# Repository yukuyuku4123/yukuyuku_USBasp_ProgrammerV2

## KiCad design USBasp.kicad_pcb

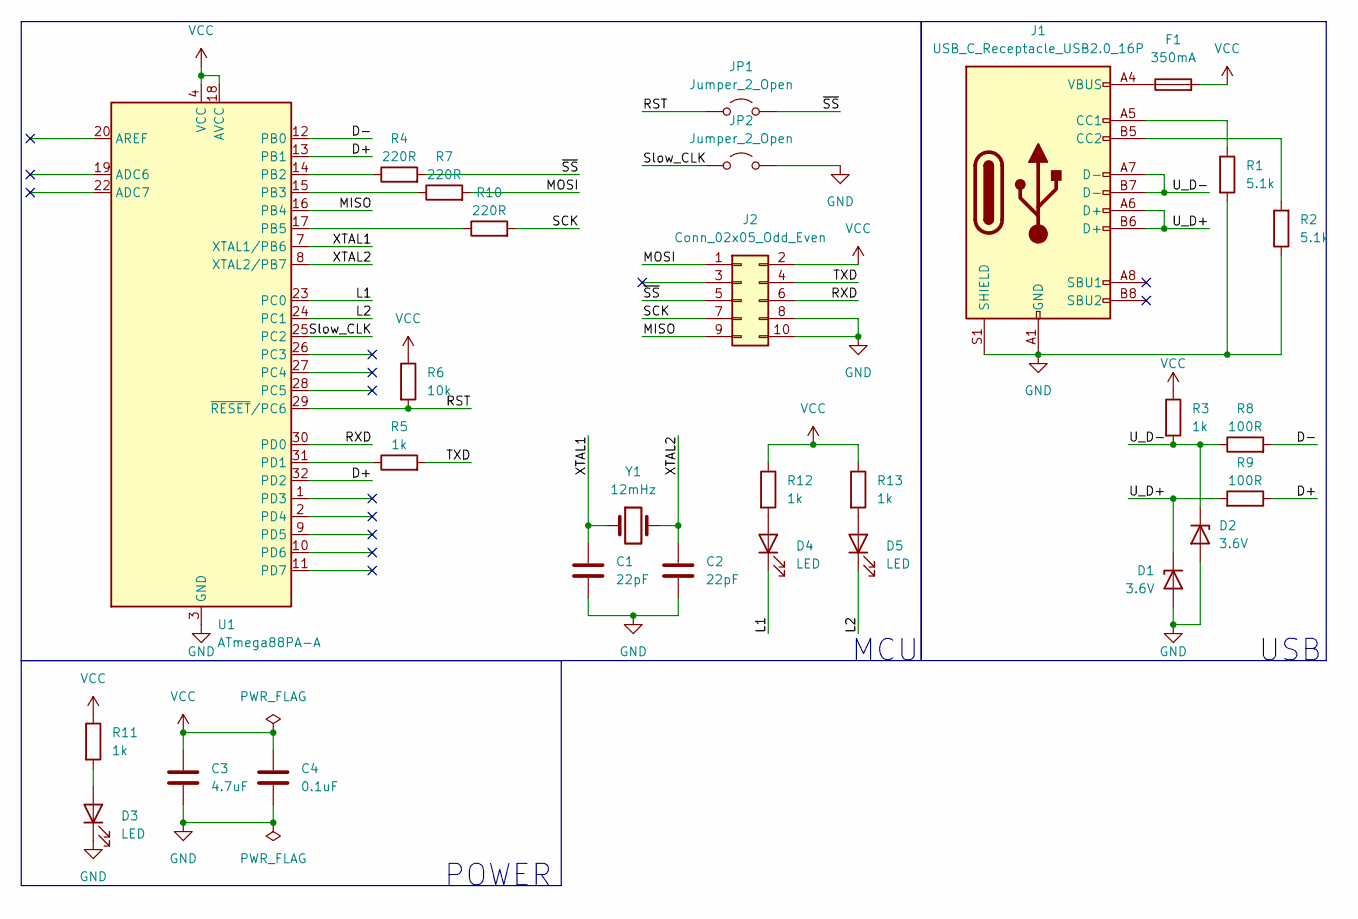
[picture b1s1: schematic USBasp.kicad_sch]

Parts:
C1, C2: 22pF; C_0402_1005Metric
C3: 4.7uF; C_0603_1608Metric
C4: 0.1uF; C_0402_1005Metric
D1, D2: 3.6V; D_SOD-323F
D3, D4, D5: LED; LED_0603_1608Metric
F1: 350mA; Fuse_0603_1608Metric
J1: USB_C_Receptacle_USB2.0_16P; USB_C_Receptacle_GCT_USB4105-xx-A_16P_TopMnt_Horizontal
J2: Conn_02x05_Odd_Even; PinHeader_2x05_P2.54mm_Vertical
JP1, JP2: Jumper_2_Open; PinHeader_1x02_P2.54mm_Vertical
R1, R2: 5.1k; R_0603_1608Metric
R3, R5, R11, R12, R13: 1k; R_0603_1608Metric
R4, R7, R10: 220R; R_0603_1608Metric
R6: 10k; R_0603_1608Metric
R8, R9: 100R; R_0603_1608Metric
U1: ATmega88PA-A; TQFP-32_7x7mm_P0.8mm
Y1: 12mHz; Crystal_HC49-4H_Vertical

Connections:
/D+: R9.1, U1.13 (PB1), U1.32 (PD2)
/D-: R8.2, U1.12 (PB0)
/L1: D4.1 (K), U1.23 (PC0)
/L2: D5.1 (K), U1.24 (PC1)
/MISO: J2.9, U1.16 (PB4)
/MOSI: J2.1, R7.2
/RST: JP1.1 (A), R6.2, U1.29 (~RESET/PC6)
/RXD: J2.6, U1.30 (PD0)
/SCK: J2.7, R10.2
/Slow_CLK: JP2.1 (A), U1.25 (PC2)
/TXD: J2.4, R5.2
/U_D+: D1.1 (K), J1.A6 (D+), J1.B6 (D+), R9.2
/U_D-: D2.1 (K), J1.A7 (D-), J1.B7 (D-), R3.2, R8.1
/XTAL1: C1.1, U1.7 (XTAL1/PB6), Y1.1
/XTAL2: C2.1, U1.8 (XTAL2/PB7), Y1.2
/~SS: J2.5, JP1.2 (B), R4.2
GND: C1.2, C2.2, C3.2, C4.2, D1.2 (A), D2.2 (A), D3.1 (K), J1.A1 (GND), J1.A12 (GND), J1.B1 (GND), J1.B12 (GND), J1.S1 (SHIELD), J2.8, J2.10, JP2.2 (B), R1.2, R2.1, U1.3 (GND), U1.5 (GND), U1.21 (GND)
unnamed: D3.2 (A), R11.2
unnamed: D4.2 (A), R12.2
unnamed: D5.2 (A), R13.2
unnamed: F1.1, J1.A4 (VBUS), J1.A9 (VBUS), J1.B4 (VBUS), J1.B9 (VBUS)
unnamed: J1.A5 (CC1), R1.1
unnamed: J1.B5 (CC2), R2.2
unnamed: R4.1, U1.14 (PB2)
unnamed: R7.1, U1.15 (PB3)
unnamed: R10.1, U1.17 (PB5)
unnamed: R5.1, U1.31 (PD1)
VCC: C3.1, C4.1, F1.2, J2.2, R3.1, R6.1, R11.1, R12.1, R13.1, U1.4 (VCC), U1.6 (VCC), U1.18 (AVCC)

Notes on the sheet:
USB
MCU
POWER

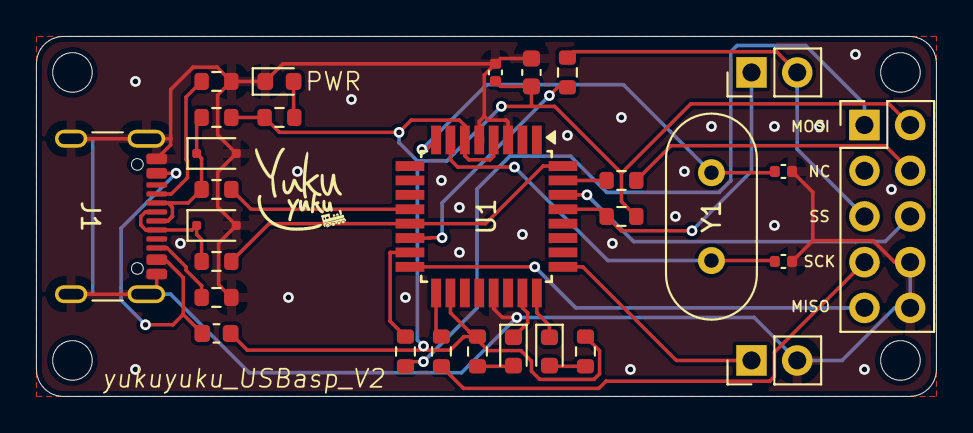
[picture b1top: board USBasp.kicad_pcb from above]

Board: 2 copper layers, 50.0 x 20.0 mm, 29 parts (0 on the bottom side), 28 nets.

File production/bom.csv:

Designator,Footprint,Quantity,Value,LCSC Part #
"C1, C2",0402,2,22pF,
C3,0603,1,4.7uF,
C4,0402,1,0.1uF,
"D1, D2",D_SOD-323F,2,3.6V,
"D3, D4, D5",0603,3,LED,
F1,0603,1,350mA,
J1,USB_C_Receptacle_GCT_USB4105-xx-A_16P_TopMnt_Horizontal,1,USB_C_Receptacle_USB2.0_16P,
J2,PinHeader_2x05_P2.54mm_Vertical,1,Conn_02x05_Odd_Even,
"JP1, JP2",PinHeader_1x02_P2.54mm_Vertical,2,Jumper_2_Open,
"R1, R2",0603,2,5.1k,
"R10, R4, R7",0603,3,220R,
"R11, R12, R13, R3, R5",0603,5,1k,
R6,0603,1,10k,
"R8, R9",0603,2,100R,
U1,TQFP-32_7x7mm_P0.8mm,1,ATmega88PA-A,
Y1,Crystal_HC49-4H_Vertical,1,12mHz,

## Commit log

2024-08-12 Ver-1.0
2024-08-12 Create LICENSE
